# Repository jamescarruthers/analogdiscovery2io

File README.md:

# Interface board for Digilent Analog Discovery 2

**Rev-a has been tested and confirmed to work, Rev-b has not been tested yet**

A board to interface anything that uses 3.5mm mono jacks (synthesisers etc) with the Digilent Analog Discovery 2 oscilloscope/wave generator/logic analyser.

Provides access to both scope channels, wave generators, triggers plus DIO 0 to 7 via 3.5mm mono jacks. DIO 8 to 15 and V+/V-/Ground via pin headers. The negative differential scope channels are connected to ground.

Note that the wave generator can output -+5V, however the DIO only 3.3V. This board does not implement any kind of level shifting, so if you're testing inputs with the output of the DIO channels then your module needs to work with 3.3V gates/triggers.

Connects directly to the AD2 with a female header. I made this as an edge connector — so you can use a 2x15 or two 1x15 straight headers.

Note; the digital I/O (including triggers) on the AD2 supports overvoltage up to -+20V. Rev-b includes resistors on all jack sockets except the scope channels. Suggest 1k on the wave generator (denoted with a dot) and 10k on the DIO.

There are 3mm holes in each corner for stand offs to support the board.

* 14 qty Thonkiconn jack sockets; https://www.thonk.co.uk/shop/3-5mm-jacks/
* 1 qty single row 15-pin female header (cheaper) -or- double row 2x15 female header (a bit more expensive)
* 4 qty 3x1 pin headers (female if you want to use male-male jumpers wires etc)
* 1 qty 9x1 pin headers (female if you want to use male-male jumpers wires etc)
* 2 qty 1k 0603 resistor
* 10 qty 10k 0603 resistor
* 4 x M3 stand offs plus screws

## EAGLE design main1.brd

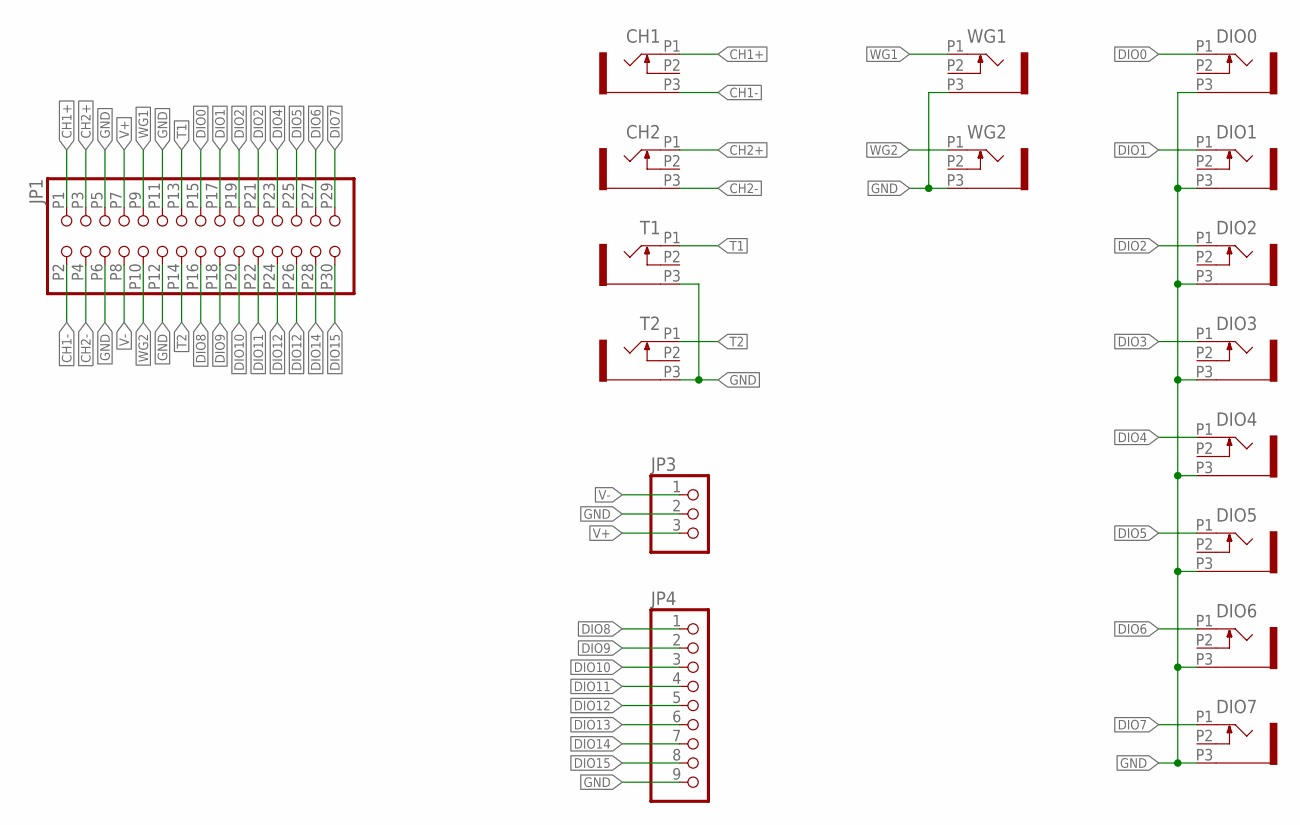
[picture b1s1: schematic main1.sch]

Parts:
CH1, CH2: THONKICONN; WQP-PJ301M-12_JACK
DIO0, DIO1, DIO2, DIO3, DIO4, DIO5, DIO6, DIO7: THONKICONN; WQP-PJ301M-12_JACK
JP1: PINHD-2X15; 2X15/EDGE
JP3: PINHD-1X3/OCT; 1X03/OCT
JP4: PINHD-1X9/OCT; 1X09/OCT
T1, T2: THONKICONN; WQP-PJ301M-12_JACK
WG1, WG2: THONKICONN; WQP-PJ301M-12_JACK

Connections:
CH1+: CH1.P1 (2), JP1.P1 (1)
CH1-: CH1.P3 (1), JP1.P2 (2)
CH2+: CH2.P1 (2), JP1.P3 (3)
CH2-: CH2.P3 (1), JP1.P4 (4)
DIO0: DIO0.P1 (2), JP1.P15 (15)
DIO1: DIO1.P1 (2), JP1.P17 (17)
DIO2: DIO2.P1 (2), JP1.P19 (19)
DIO3: DIO3.P1 (2), JP1.P21 (21)
DIO4: DIO4.P1 (2), JP1.P23 (23)
DIO5: DIO5.P1 (2), JP1.P25 (25)
DIO6: DIO6.P1 (2), JP1.P27 (27)
DIO7: DIO7.P1 (2), JP1.P29 (29)
DIO8: JP1.P16 (16), JP4.1
DIO9: JP1.P18 (18), JP4.2
DIO10: JP1.P20 (20), JP4.3
DIO11: JP1.P22 (22), JP4.4
DIO12: JP1.P24 (24), JP4.5
DIO13: JP1.P26 (26), JP4.6
DIO14: JP1.P28 (28), JP4.7
DIO15: JP1.P30 (30), JP4.8
GND: DIO0.P3 (1), DIO1.P3 (1), DIO2.P3 (1), DIO3.P3 (1), DIO4.P3 (1), DIO5.P3 (1), DIO6.P3 (1), DIO7.P3 (1), JP1.P5 (5), JP1.P6 (6), JP1.P11 (11), JP1.P12 (12), JP3.2, JP4.9, T1.P3 (1), T2.P3 (1), WG1.P3 (1), WG2.P3 (1)
T1: JP1.P13 (13), T1.P1 (2)
T2: JP1.P14 (14), T2.P1 (2)
V+: JP1.P7 (7), JP3.3
V-: JP1.P8 (8), JP3.1
WG1: JP1.P9 (9), WG1.P1 (2)
WG2: JP1.P10 (10), WG2.P1 (2)

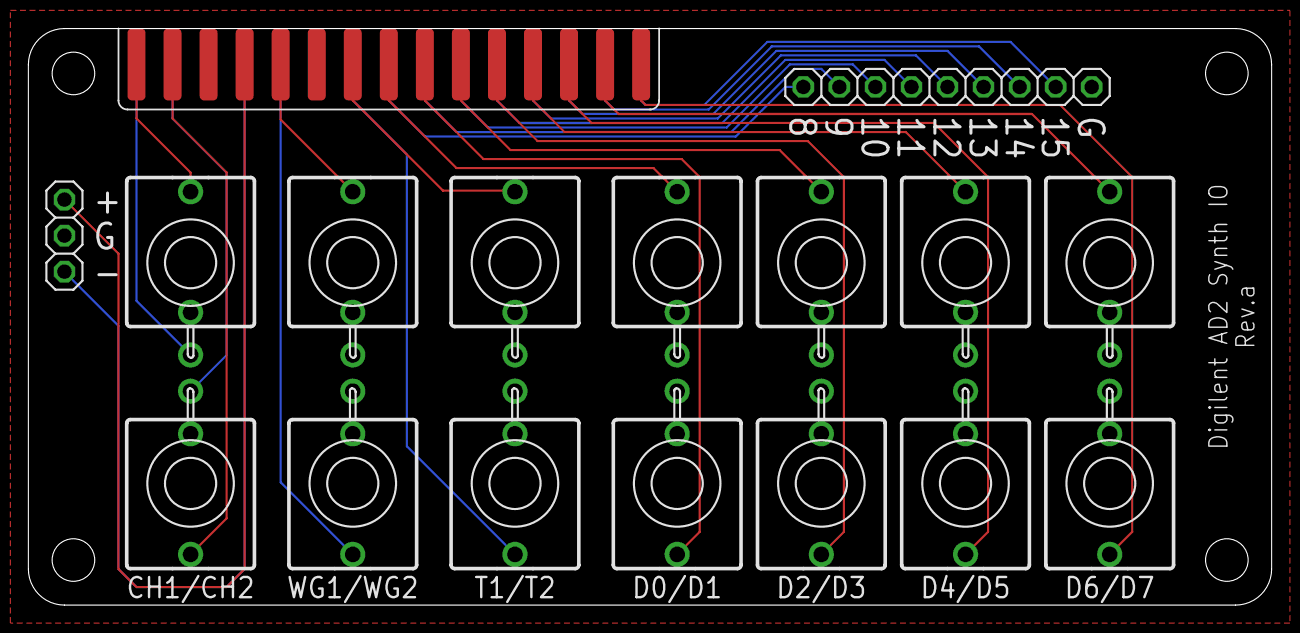
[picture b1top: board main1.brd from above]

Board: 2 copper layers, 87.6 x 40.6 mm, 17 parts (0 on the bottom side), 27 nets.

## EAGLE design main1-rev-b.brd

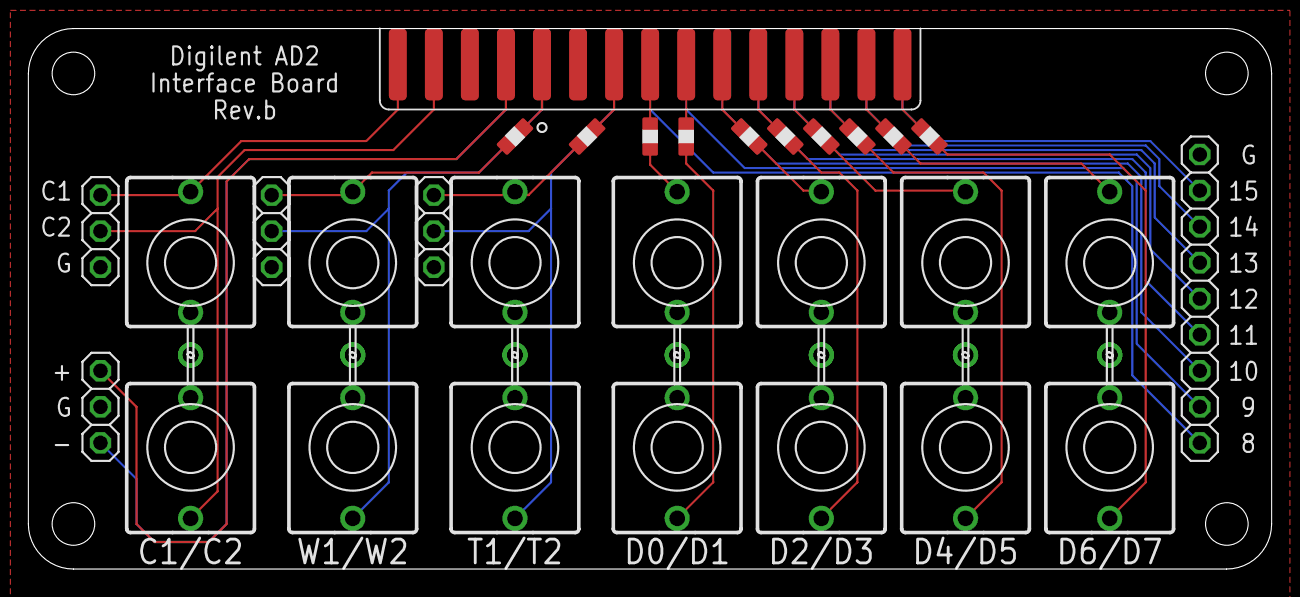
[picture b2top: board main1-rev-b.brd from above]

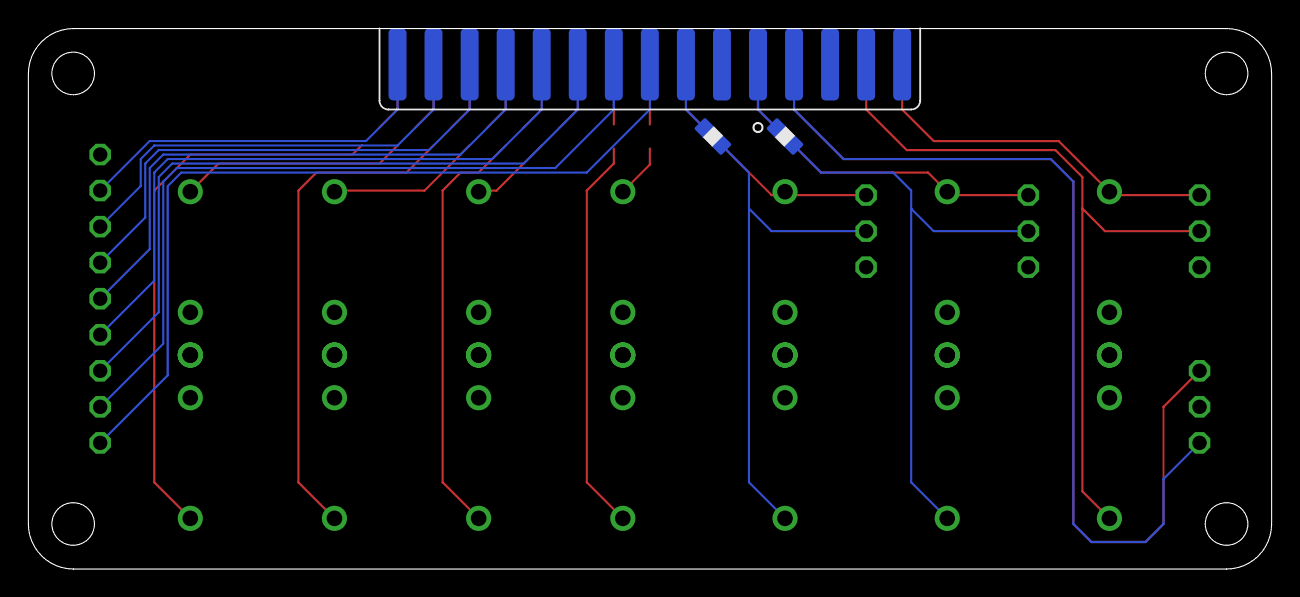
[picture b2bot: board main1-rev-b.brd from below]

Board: 2 copper layers, 87.6 x 38.1 mm, 36 parts (2 on the bottom side), 37 nets.

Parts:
CH1, CH2: THONKICONN; WQP-PJ301M-12_JACK
DIO0, DIO1, DIO2, DIO3, DIO4, DIO5, DIO6, DIO7: THONKICONN; WQP-PJ301M-12_JACK
JP1: 2X15/EDGE
JP2, JP3, JP5, JP6: 1X03/OCT
JP4: 1X09/OCT
R0, R1, R2, R3, R4, R5, R6, R7, R8, R9: 103; R0603
R10, R11: 102; R0603
T1, T2: THONKICONN; WQP-PJ301M-12_JACK
U$1, U$2, U$3, U$4: HOLE_3MM
WG1, WG2: THONKICONN; WQP-PJ301M-12_JACK

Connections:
CH1+: CH1.P1, JP1.P1, JP2.1
CH2+: CH2.P1, JP1.P3, JP2.2
DIO0: JP1.P15, R0.1
DIO0_: DIO0.P1, R0.2
DIO1: JP1.P17, R1.1
DIO1_: DIO1.P1, R1.2
DIO2: JP1.P19, R2.1
DIO2_: DIO2.P1, R2.2
DIO3: JP1.P21, R3.1
DIO3_: DIO3.P1, R3.2
DIO4: JP1.P23, R4.1
DIO4_: DIO4.P1, R4.2
DIO5: JP1.P25, R5.1
DIO5_: DIO5.P1, R5.2
DIO6: JP1.P27, R6.1
DIO6_: DIO6.P1, R6.2
DIO7: JP1.P29, R7.1
DIO7_: DIO7.P1, R7.2
DIO8: JP1.P16, JP4.1
DIO9: JP1.P18, JP4.2
DIO10: JP1.P20, JP4.3
DIO11: JP1.P22, JP4.4
DIO12: JP1.P24, JP4.5
DIO13: JP1.P26, JP4.6
DIO14: JP1.P28, JP4.7
DIO15: JP1.P30, JP4.8
GND: CH1.P3, CH2.P3, DIO0.P3, DIO1.P3, DIO2.P3, DIO3.P3, DIO4.P3, DIO5.P3, DIO6.P3, DIO7.P3, JP1.P2, JP1.P4, JP1.P5, JP1.P6, JP1.P11, JP1.P12, JP2.3, JP3.2, JP4.9, JP5.3, JP6.3, T1.P3, T2.P3, WG1.P3, WG2.P3
T1: JP1.P13, R8.1
T1_: JP6.1, R8.2, T1.P1
T2: JP1.P14, R9.1
T2_: JP6.2, R9.2, T2.P1
V+: JP1.P7, JP3.3
V-: JP1.P8, JP3.1
WG1: JP1.P9, R10.1
WG1_: JP5.1, R10.2, WG1.P1
WG2: JP1.P10, R11.1
WG2_: JP5.2, R11.2, WG2.P1

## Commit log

2017-01-27 Rename main1.brd to main1_rev-a.brd
2017-01-27 Rename main1.sch to main1-rev-a.sch
2017-01-27 Rename main2.brd to main1-rev-b.brd
2017-01-27 Rename main2.sch to main1-rev-b.sch
2017-03-27 Add Gitter badge
2017-05-03 Renamed files
